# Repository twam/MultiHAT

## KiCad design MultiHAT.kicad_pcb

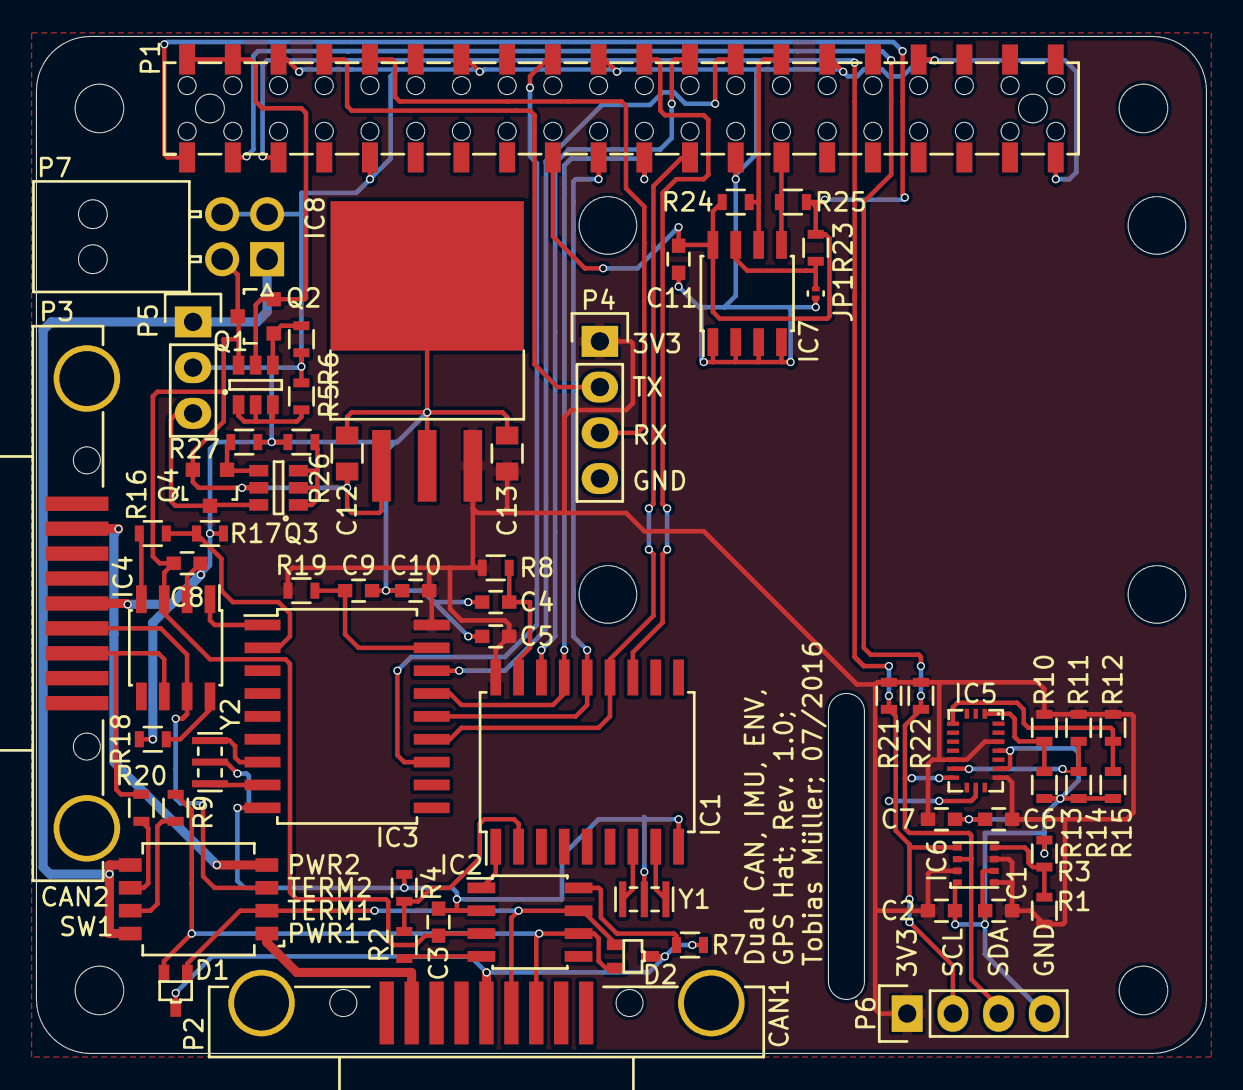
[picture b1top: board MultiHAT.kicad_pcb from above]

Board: 2 copper layers, 65.0 x 56.5 mm, 69 parts (0 on the bottom side), 51 nets.

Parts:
C1, C2, C3, C4, C5, C6, C7, C8, C9, C10, C11: 100n; C_0603
C12, C13: 4u7; C_0805
D1, D2: PESD1CAN; SOT-323
IC1, IC3: MCP2515-x/SO; SOIC-18_7.5x11.6mm_Pitch1.27mm
IC2, IC4: MCP2551; SOIC-8_3.9x4.9mm_Pitch1.27mm
IC5: BMX055
IC6: BME280
IC7: CAT24C32; SOIC-8_3.9x4.9mm_Pitch1.27mm
IC8: MCP1826S; 3-DDPAK
JP1: Jumper_NO_Small; R_0201
MountingHole_2-7mm, MountingHole_2-7mm#2, MountingHole_2-7mm#3, MountingHole_2-7mm#4: VAL**; MountingHole_2-7mm
P1: RASPBERRY_PI; REF-182665-01-BOTTOM-ENTRY
P2: CAN1; K202XHT-E9S-N
P3: CAN2; K202XHT-E9S-N
P4: GPS; Pin_Header_Straight_1x04
P5: SMPS; Pin_Header_Straight_1x03
P6: I2C; Pin_Header_Straight_1x04
P7: POWER; Molex_NanoFit_2x02x2.50mm_Angled
Q1, Q3: DMMT5401; SOT-23-6
Q2, Q4: DMG2305UX; SOT-23
R1, R3, R10, R11, R12, R13, R14, R15, R23: 100k; R_0603
R2, R5, R16, R26: 10k; R_0603
R4, R17: 22k; R_0603
R6, R27: 47k; R_0603
R7, R8, R18, R19, R21, R22: 4k7; R_0603
R9, R20: 120R; R_0603
R24, R25: 3k9; R_0603
SW1: SPST-4; GDH04S04
Y1, Y2: PRQV16.00CR5010Y000; PRQV-C

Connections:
+3V3: C1.2, C2.2, C5.2, C6.2, C7.2, C10.2, C13.1, IC1.18, IC3.18, IC5.3, IC5.7, IC5.13, IC6.2, IC6.6, IC6.8, IC8.3, P4.1, P6.1, R1.1, R8.1, R10.1, R11.1, R12.1, R19.1, R21.2, R22.2
+5V: C3.2, C8.2, C12.2, IC2.3, IC4.3, IC8.1, P7.3, Q1.6, Q2.3, Q3.5, Q4.2
+12V: P5.1, P7.1, SW1.5, SW1.8
/CAN1H: D1.1, D2.1, IC2.7, P2.7, SW1.2
/CAN1L: D1.2, D2.2, IC2.6, P2.2, R9.1
/CAN1_INT: IC1.12, P1.22
/CAN1_RX: IC2.4, R2.1
/CAN1_TX: IC1.1, IC2.1
/CAN1_VDD: P2.9, SW1.1
/CAN2H: IC4.7, P3.7, SW1.3
/CAN2L: IC4.6, P3.2, R20.1
/CAN2_INT: IC3.12, P1.18
/CAN2_RX: IC4.4, R16.1
/CAN2_TX: IC3.1, IC4.1
/CAN2_VDD: P3.9, SW1.4
/I2C_SCL: IC5.9, IC6.4, P1.5, P6.2, R21.1
/I2C_SDA: IC5.11, IC6.3, P1.3, P6.3, R22.1
/ID_SCL: IC7.6, P1.28, R24.2
/ID_SDA: IC7.5, P1.27, R25.2
/PI_3V3: C11.2, IC7.8, P1.1, P1.17, R23.1, R24.1, R25.1
/PI_5V0: P1.2, P1.4, Q1.5, Q2.2
/RXD0: P1.10, P4.3
/SPI_CE0: IC1.16, P1.24
/SPI_CE1: IC3.16, P1.26
/SPI_CLK: IC1.13, IC3.13, P1.23
/SPI_MISO: IC1.15, IC3.15, P1.21
/SPI_MOSI: IC1.14, IC3.14, P1.19
/TXD0: P1.8, P4.2
GND: C1.1, C2.1, C3.1, C4.1, C5.1, C6.1, C7.1, C8.1, C9.1, C10.1, C11.1, C12.1, C13.2, D1.3, D2.3, IC1.9, IC2.2, IC3.9, IC4.2, IC5.4, IC5.6, IC6.1, IC6.7, IC7.1, IC7.2, IC7.3, IC7.4, IC8.2, IC8.4, JP1.2, P1.6, P1.9, P1.14, P1.20, P1.25, P1.30, P1.34, P1.39, P2.3, P3.3, P4.4, P5.2, P6.4, P7.2, P7.4, R3.2, R4.1, R5.2, R6.2, R7.2, R13.2, R14.2, R15.2, R17.1, R18.2, R26.2, R27.2, Y1.2, Y2.2
unnamed: C4.2, IC1.17, R8.2
unnamed: C9.2, IC3.17, R19.2
unnamed: IC1.2, R2.2, R4.2
unnamed: IC1.7, Y1.3
unnamed: IC1.8, Y1.1
unnamed: IC2.8, R7.1
unnamed: IC3.2, R16.2, R17.2
unnamed: IC3.7, Y2.3
unnamed: IC3.8, Y2.1
unnamed: IC4.8, R18.1
unnamed: IC5.12, R11.2, R14.1
unnamed: IC5.17, R12.2, R15.1
unnamed: IC5.20, R10.2, R13.1
unnamed: IC6.5, R1.2, R3.1
unnamed: IC7.7, JP1.1, R23.2
unnamed: P5.3, Q3.6, Q4.3
unnamed: Q1.1, Q1.2, Q1.3, R5.1
unnamed: Q1.4, Q2.1, R6.1
unnamed: Q3.1, Q3.2, Q3.3, R26.1
unnamed: Q3.4, Q4.1, R27.1
unnamed: R9.2, SW1.7
unnamed: R20.2, SW1.6

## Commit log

2016-09-25 Initial commit. Rev. 1
2016-09-25 Gerber Rev. 1

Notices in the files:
MultiHAT.kicad_pcb:
License: CC-BY-SA 4.0
